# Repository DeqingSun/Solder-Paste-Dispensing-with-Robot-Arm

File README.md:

# Solder Paste Dispensing with Robot Arm

This is an open-sourced project that dispenses solder paste on PCB with a robot arm and Raspberry Pi. 

This project uses an off-shelf Dobot Magician as the robot arm part. The customized end effector dispenses solder paste. And another laser jig calibrates the position of the robot arm. 

## Hardware 

* Dobot Magician

A consumer-grade robot arm with an embed control box. 

* Raspberry Pi 3B

The Raspberry Pi is pretty convenient in playing with Python code. The Raspberry Pi hosted all files and run a python script. Users can use a browser on a computer or smartphone to control the robot arm with the Raspberry Pi. It's very easy to set up the Jupyter Notebook on the new version of Raspberry Pi OS, which saves a lot of time in debugging.

* 3D Printed Laser Jig

The laser jig uses 2 pairs of laser modules and photoresistors to calibrate the robot arm. There is also an auto-level sensor to fine-tune the Z-axis. The whole jig is controlled by an Arduino Micro Pro.

* 3D Printed solder paste dispenser

The solder paste dispenser is syringe driven by a stepper motor. There is also a heater attached to the needle to reduce the viscosity of the paste.

## Detail of the solder paste dispenser

The solder paste dispenser uses a NEMA 42 stepper motor. Dobot Magician has 2 external motor drivers. However, the driving current is not adjustable. So a heatsink may be needed. The stepper is attached to a T5*1 leading screw with coupling, and the flange nut is attached to the piston with an adaptor and a #4-1/2 sheet metal screw. The syringe is a Nordson EFD 30cc one. And the needle is an 18 gauge one. Also, there is a 70C PTC heating element that keeps the needle warm to reduce the viscosity of the paste.

## Detail of the laser jig

The laser jig is taped on a silicon pad for extra friction and Z-axis tolerance.  

## Why using a robot arm?

Most solder paste dispenser uses a Cartesian platform. A Cartesian platform is generally more accurate and rigid. But the machine is generally much bigger than its working area. The robot arm saves space. When the robot arm is not used, it only takes 40 sq in of desk space. Pretty neat for prototyping.    

## Why a laser jig?

A robot arm often has good repeatability and bad accuracy. With a laser-guided jig, the robot arm can get the position and orientation of target PCB accurately.

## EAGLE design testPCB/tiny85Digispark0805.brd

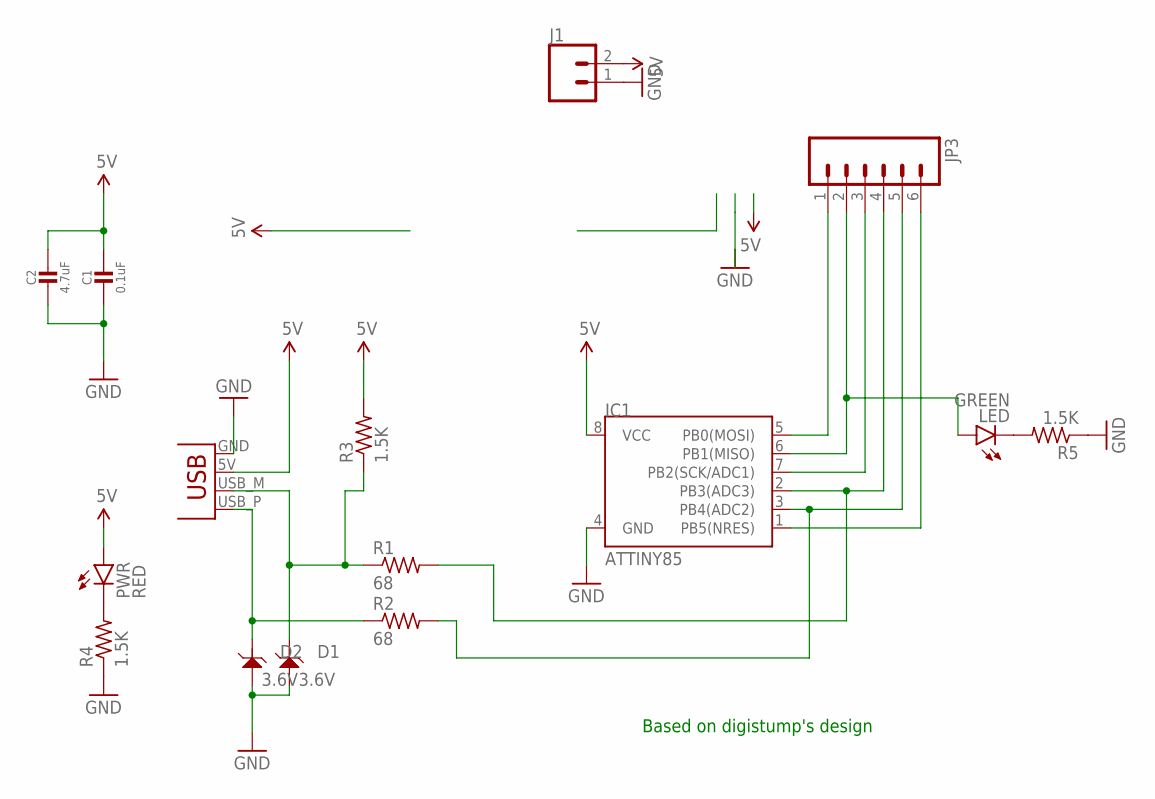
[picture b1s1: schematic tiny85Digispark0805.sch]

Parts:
C1: 0.1uF; 0805-NO
C2: 4.7uF; 0805-NO
D1, D2: 3.6V; SOD-123; LCSC C82565
IC1: ATTINY85; SO08-EIAJ
J1: CONN_02; 1X02
JP3: M06SIP; 1X06
LED: GREEN; CHIP-LED0805
PWR: RED; CHIP-LED0805
R1, R2: 68; M0805
R3, R4, R5: 1.5K; M0805
X1: USBPCB; USB-A-PCB

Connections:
5V: C1.1, C2.1, IC1.8 (VCC), J1.2, PWR.A, R3.2, X1.5V (VBUS)
GND: C1.2, C2.2, D1.+ (1), D2.+ (1), IC1.4 (GND), J1.1, R4.1, R5.1, X1.GND
unnamed: PWR.C, R4.2
unnamed: LED.C, R5.2
PB0: IC1.5 (PB0(MOSI)), JP3.1
PB1: IC1.6 (PB1(MISO)), JP3.2, LED.A
PB2: IC1.7 (PB2(SCK/ADC1)), JP3.3
PB3: IC1.2 (PB3(ADC3)), JP3.4, R1.2
PB4: IC1.3 (PB4(ADC2)), JP3.5, R2.2
PB5: IC1.1 (PB5(NRES)), JP3.6
USBM: D1.- (2), R1.1, R3.1, X1.USB_M (D-)
USBP: D2.- (2), R2.1, X1.USB_P (D+)

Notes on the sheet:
Based on digistump's design

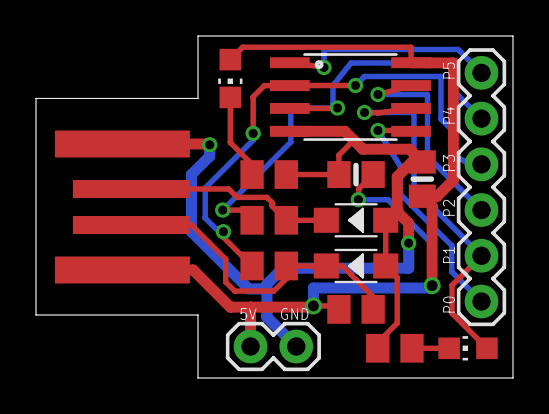
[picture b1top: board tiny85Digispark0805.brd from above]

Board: 2 copper layers, 26.5 x 19.0 mm, 15 parts (0 on the bottom side), 12 nets.

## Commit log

2020-06-29 add 3d model
2020-06-30 add imgs
2020-06-30 add laser jig and code
2020-06-30 add python code and PCB files

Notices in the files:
testPCB/tiny85Digispark0805.brd:
The Digispark design (schematic, layout, concept) is licensed under the Creative Commons Attribution-ShareAlike 3.0 Unported License: http://creativecommons.org/licenses/by-sa/3.0
Digispark name. logo and Digistump name, logo Copyright 2013 Digistump LLC All Rights Reserved
parts and their libraries:
SparkFun: Licensing: CC v3.0 Share-Alike You are welcome to use this library for commercial purposes.
SparkFun-Connectors: Licensing: Creative Commons ShareAlike 4.0 International - https://creativecommons.org/licenses/by-sa/4.0
